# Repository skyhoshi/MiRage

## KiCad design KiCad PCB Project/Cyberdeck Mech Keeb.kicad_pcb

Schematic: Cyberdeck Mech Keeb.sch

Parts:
C3, C16, C17, C22: 0.1uF; C0603
CN1, CN2: AUDIO-JACK3; AUDIO-JACK-TRRS-SMD
IC1, IC3: PCA9505; TSSOP56-6
J1, J2, J3, J5: SOLDERJUMPERTRACE; SJ_2S-TRACE
JP1, JP2: PINHD-1X4_90; 1X04_90
JP3: PINHD-2X7; 2X07
MOD1: MOUDLE-SEEEDUINO-XIAO; MOUDLE14P-2.54-21X17.8MM
MOD2, MOD3, MOD4: DISPLAY-OLED-128X64-I2C
R1, R2, R3, R4: 4.7k; R0603
SW1, SW2, SW3, SW4, SW5, SW6: SPST_TACT-EVQQ2; EVQ-Q2
SW7, SW8, SW9, SW10, SW11, SW12, SW13, SW14, SW15, SW16, SW17, SW18, SW19, SW20, SW21, SW22, SW23, SW24, SW25, SW26, SW27, SW28, SW29, SW30, SW31, SW32, SW33, SW34, SW35, SW36, SW37, SW38, SW39, SW40, SW41, SW42, SW43, SW44, SW45, SW46, SW47, SW48, SW49, SW50, SW51, SW52, SW53, SW54, SW55, SW56, SW57, SW58, SW59, SW60, SW61, SW62, SW63: KEYSWITCH-PLAIN-CHOC-1U; CHOC-1U

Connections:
+3V3: C3.1, C16.1, CN1.TIP, IC1.6 (VSS@1), IC1.11 (VSS@2), IC1.23 (VSS@3), IC1.27 (A0), IC1.28 (A1), IC1.29 (A2), IC1.34 (VSS@4), IC1.39 (VSS@5), IC1.51 (VSS@6), J5.2, JP1.1, JP3.6, MOD1.12 (3V3), MOD2.2 (VCC), MOD3.2 (VCC), MOD4.2 (VCC), R1.2, R2.2, R3.2, R4.2
/D0: JP3.1, MOD1.1 (PA02_A0_D0)
/D1: JP3.3, MOD1.2 (PA4_A1_D1)
/D2: JP3.5, MOD1.3 (PA10_A2_D2)
/D3: JP3.7, MOD1.4 (PA11_A3_D3)
/D8: JP3.12, MOD1.9 (PA7_A8_D8_SCK)
/D9: JP3.10, MOD1.10 (PA5_A9_D9_MISO)
/D10: JP3.8, MOD1.11 (PA6_A10_D10_MOSI)
/SCL: CN1.RING1, IC1.2 (SCL), J3.2, JP1.2, JP3.11, MOD1.6 (PA9_A5_D5_SCL), MOD2.3 (SCL), MOD3.3 (SCL), R2.1
/SCL2: JP3.13, MOD1.8 (PB09_A7_D7_RX), MOD4.3 (SCL), R4.1
/SCL': CN2.RING1, IC3.2 (SCL), J3.1, JP2.3
/SDA: CN1.RING2, IC1.1 (SDA), J2.2, JP1.3, JP3.9, MOD1.5 (PA8_A4_D4_SDA), MOD2.4 (SDA), MOD3.4 (SDA), R1.1
/SDA2: JP3.14, MOD1.7 (PB08_A6_D6_TX), MOD4.4 (SDA), R3.1
/SDA': CN2.RING2, IC3.1 (SDA), J2.1, JP2.2
/VIN: JP3.2, MOD1.14 (5V)
/~INTERRUPT: IC1.55 (~INT)
/~INTERRUPT': IC3.55 (~INT)
/~RESET: IC1.56 (~RESET)
/~RESET': IC3.56 (~RESET)
GND: C3.2, C16.2, CN1.EARTH, IC1.18 (VDD@1), IC1.30 (~OE), IC1.46 (VDD@2), J1.2, JP1.4, JP3.4, MOD1.13 (GND), MOD2.1 (GND), MOD3.1 (GND), MOD4.1 (GND), SW1.A, SW2.A, SW3.A, SW4.A, SW5.A, SW6.A, SW14.CHOC2 (P1), SW15.CHOC2 (P1), SW16.CHOC2 (P1), SW17.CHOC2 (P1), SW18.CHOC2 (P1), SW26.CHOC2 (P1), SW27.CHOC2 (P1), SW28.CHOC2 (P1), SW29.CHOC2 (P1), SW30.CHOC2 (P1), SW38.CHOC2 (P1), SW39.CHOC2 (P1), SW40.CHOC2 (P1), SW41.CHOC2 (P1), SW42.CHOC2 (P1), SW50.CHOC2 (P1), SW51.CHOC2 (P1), SW52.CHOC2 (P1), SW53.CHOC2 (P1), SW54.CHOC2 (P1), SW58.CHOC2 (P1), SW59.CHOC2 (P1), SW60.CHOC2 (P1), SW62.CHOC2 (P1)
GND2: C17.2, C22.2, CN2.EARTH, IC3.18 (VDD@1), IC3.29 (A2), IC3.30 (~OE), IC3.46 (VDD@2), J1.1, JP2.1, SW7.CHOC2 (P1), SW8.CHOC2 (P1), SW9.CHOC2 (P1), SW10.CHOC2 (P1), SW11.CHOC2 (P1), SW12.CHOC2 (P1), SW13.CHOC2 (P1), SW19.CHOC2 (P1), SW20.CHOC2 (P1), SW21.CHOC2 (P1), SW22.CHOC2 (P1), SW23.CHOC2 (P1), SW24.CHOC2 (P1), SW25.CHOC2 (P1), SW31.CHOC2 (P1), SW32.CHOC2 (P1), SW33.CHOC2 (P1), SW34.CHOC2 (P1), SW35.CHOC2 (P1), SW36.CHOC2 (P1), SW37.CHOC2 (P1), SW43.CHOC2 (P1), SW44.CHOC2 (P1), SW45.CHOC2 (P1), SW46.CHOC2 (P1), SW47.CHOC2 (P1), SW48.CHOC2 (P1), SW49.CHOC2 (P1), SW55.CHOC2 (P1), SW56.CHOC2 (P1), SW57.CHOC2 (P1), SW61.CHOC2 (P1), SW63.CHOC2 (P1)
unnamed: IC1.3 (IO0_0), SW30.CHOC1 (P0)
unnamed: IC1.4 (IO0_1), SW29.CHOC1 (P0)
unnamed: IC1.5 (IO0_2), SW28.CHOC1 (P0)
unnamed: IC1.7 (IO0_3), SW27.CHOC1 (P0)
unnamed: IC1.8 (IO0_4), SW26.CHOC1 (P0)
unnamed: IC1.9 (IO0_5), SW42.CHOC1 (P0)
unnamed: IC1.10 (IO0_6), SW41.CHOC1 (P0)
unnamed: IC1.12 (IO0_7), SW40.CHOC1 (P0)
unnamed: IC1.13 (IO1_0), SW39.CHOC1 (P0)
unnamed: IC1.14 (IO1_1), SW38.CHOC1 (P0)
unnamed: IC1.15 (IO1_2), SW54.CHOC1 (P0)
unnamed: IC1.16 (IO1_3), SW60.CHOC1 (P0)
unnamed: IC1.19 (IO1_5), SW62.CHOC1 (P0)
unnamed: IC1.20 (IO1_6), SW59.CHOC1 (P0)
unnamed: IC1.21 (IO1_7), SW58.CHOC1 (P0)
unnamed: IC1.22 (IO2_0), SW50.CHOC1 (P0)
unnamed: IC1.24 (IO2_1), SW51.CHOC1 (P0)
unnamed: IC1.25 (IO2_2), SW52.CHOC1 (P0)
unnamed: IC1.26 (IO2_3), SW53.CHOC1 (P0)
unnamed: IC1.37 (IO3_1), SW14.CHOC1 (P0)
unnamed: IC1.38 (IO3_2), SW15.CHOC1 (P0)
unnamed: IC1.40 (IO3_3), SW16.CHOC1 (P0)
unnamed: IC1.41 (IO3_4), SW17.CHOC1 (P0)
unnamed: IC1.42 (IO3_5), SW18.CHOC1 (P0)
unnamed: IC1.43 (IO3_6), SW1.B (S)
unnamed: IC1.44 (IO3_7), SW3.B (S)
unnamed: IC1.45 (IO4_0), SW5.B (S)
unnamed: IC1.52 (IO4_5), SW2.B (S)
unnamed: IC1.53 (IO4_6), SW4.B (S)
unnamed: IC1.54 (IO4_7), SW6.B' (S1)
unnamed: IC3.9 (IO0_5), SW8.CHOC1 (P0)
unnamed: IC3.10 (IO0_6), SW9.CHOC1 (P0)
unnamed: IC3.12 (IO0_7), SW10.CHOC1 (P0)
unnamed: IC3.13 (IO1_0), SW35.CHOC1 (P0)
unnamed: IC3.14 (IO1_1), SW23.CHOC1 (P0)
unnamed: IC3.15 (IO1_2), SW11.CHOC1 (P0)
unnamed: IC3.16 (IO1_3), SW48.CHOC1 (P0)
unnamed: IC3.17 (IO1_4), SW36.CHOC1 (P0)
unnamed: IC3.19 (IO1_5), SW24.CHOC1 (P0)
unnamed: IC3.20 (IO1_6), SW12.CHOC1 (P0)
unnamed: IC3.21 (IO1_7), SW61.CHOC1 (P0)
unnamed: IC3.22 (IO2_0), SW49.CHOC1 (P0)
unnamed: IC3.24 (IO2_1), SW37.CHOC1 (P0)
unnamed: IC3.25 (IO2_2), SW25.CHOC1 (P0)
unnamed: IC3.26 (IO2_3), SW13.CHOC1 (P0)
unnamed: IC3.32 (IO2_5), SW47.CHOC1 (P0)
unnamed: IC3.33 (IO2_6), SW63.CHOC1 (P0)
unnamed: IC3.35 (IO2_7), SW57.CHOC1 (P0)
unnamed: IC3.36 (IO3_0), SW22.CHOC1 (P0)
unnamed: IC3.37 (IO3_1), SW34.CHOC1 (P0)
unnamed: IC3.38 (IO3_2), SW46.CHOC1 (P0)
unnamed: IC3.41 (IO3_4), SW21.CHOC1 (P0)
unnamed: IC3.42 (IO3_5), SW33.CHOC1 (P0)
unnamed: IC3.43 (IO3_6), SW45.CHOC1 (P0)
unnamed: IC3.44 (IO3_7), SW56.CHOC1 (P0)
unnamed: IC3.45 (IO4_0), SW20.CHOC1 (P0)
unnamed: IC3.47 (IO4_1), SW32.CHOC1 (P0)
unnamed: IC3.48 (IO4_2), SW7.CHOC1 (P0)
unnamed: IC3.49 (IO4_3), SW44.CHOC1 (P0)
unnamed: IC3.50 (IO4_4), SW19.CHOC1 (P0)
unnamed: IC3.52 (IO4_5), SW31.CHOC1 (P0)
unnamed: IC3.53 (IO4_6), SW43.CHOC1 (P0)
unnamed: IC3.54 (IO4_7), SW55.CHOC1 (P0)
VCC/2: C17.1, C22.1, CN2.TIP, IC3.6 (VSS@1), IC3.11 (VSS@2), IC3.23 (VSS@3), IC3.27 (A0), IC3.28 (A1), IC3.34 (VSS@4), IC3.39 (VSS@5), IC3.51 (VSS@6), J5.1, JP2.4

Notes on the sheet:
Seeeduino XIAO (RP2040 if possible)
VSS and VDD are reversed
These need pullups

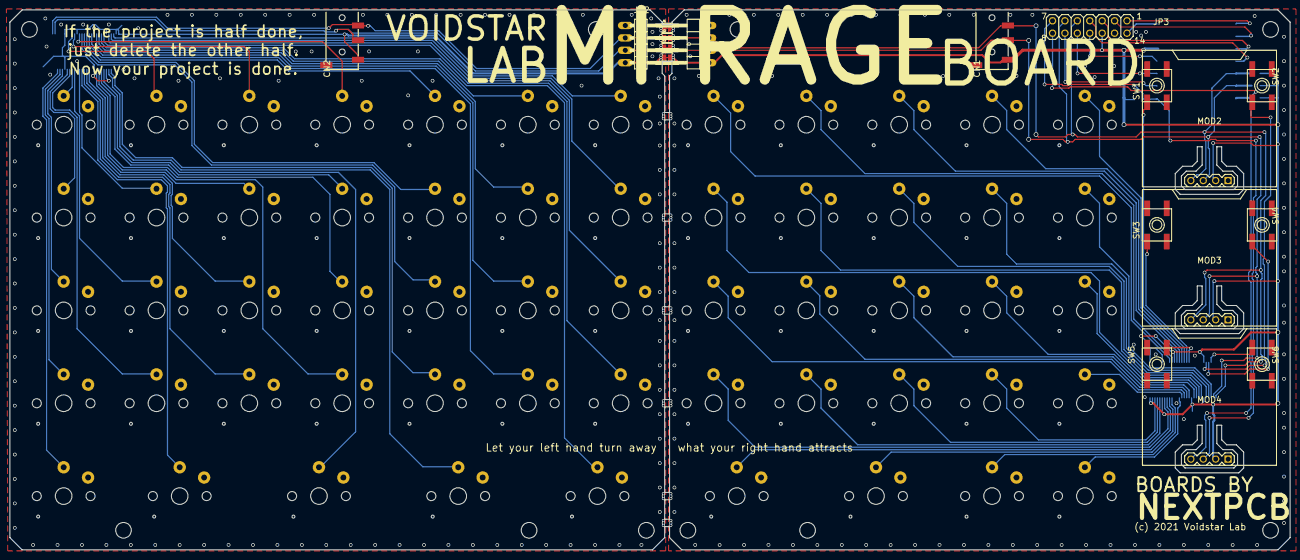
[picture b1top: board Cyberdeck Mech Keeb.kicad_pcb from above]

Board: 2 copper layers, 262.0 x 110.5 mm, 96 parts (0 on the bottom side), 81 nets.

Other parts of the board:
@HOLE0, @HOLE1, @HOLE2, @HOLE3, @HOLE4, @HOLE5, @HOLE6, @HOLE7, @HOLE8, @HOLE9: (no value)

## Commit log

2022-02-08 attempting to convert to kicad

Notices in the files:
KiCad PCB Project/Cyberdeck Mech Keeb.kicad_pcb:
(c) 2021 Voidstar Lab
(c) 2021 Voidstar Lab LLC
